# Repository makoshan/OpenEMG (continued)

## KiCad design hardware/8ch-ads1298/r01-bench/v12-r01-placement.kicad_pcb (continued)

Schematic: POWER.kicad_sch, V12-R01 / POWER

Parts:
C19: 10uF; C_0603_1608Metric
C20, C21: 22uF; C_0805_2012Metric
C22, C23, C24: 1uF; C_0402_1005Metric
C25, C31: 100nF; C_0402_1005Metric
D1: B5819WS; D_SOD-323
L1: 470nH; FTC201610S
Q1: AO3400A; SOT-23
R21, R25, R27, R29, R30, R31, R32: 100k; R_0402_1005Metric
R22, R28: 10k; R_0402_1005Metric
R23: 1k; R_0402_1005Metric
R24: 47k; R_0402_1005Metric
R26: 0R; R_0402_1005Metric
R41: 4.7k; R_0402_1005Metric
TP1: AVDD; TestPoint_Pad_D1.0mm
TP2: DVDD; TestPoint_Pad_D1.0mm
TP3: PG; TestPoint_Pad_D1.0mm
TP4: OE_N; TestPoint_Pad_D1.0mm
TP5: ADS_PWDN; TestPoint_Pad_D1.0mm
TP6: ADS_RESET; TestPoint_Pad_D1.0mm
TP7: ADS_CLKSEL; TestPoint_Pad_D1.0mm
TP8: VCAP1; TestPoint_Pad_D1.0mm
TP9: U7_EN; TestPoint_Pad_D1.0mm
TP10: GND; TestPoint_Pad_D1.0mm
U7: TPS63802DLAR; TI_DLA0010A
U9: TPS7A2018PDBVR; SOT-23-5
U12: TPS3808G33DBVR; SOT-23-6

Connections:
3V3: U12.5 (SENSE); also elsewhere on the board
ADS_CLKSEL: TP7.1; also elsewhere on the board
ADS_PWDN: TP5.1; also elsewhere on the board
ADS_RESET: TP6.1; also elsewhere on the board
ANA_EN: R24.1; also elsewhere on the board
AVDD: C20.1, C21.1, C22.1, D1.1 (K), R21.1, R29.1, TP1.1, U7.6 (VOUT), U9.1 (IN), U9.3 (EN); also elsewhere on the board
AVDD_SENSE: C25.1, R31.2, R32.1; also elsewhere on the board
AVS1: R29.2, R30.1
AVS2: R30.2, R31.1
DVDD: C23.1, D1.2 (A), R28.2, TP2.1, U9.5 (OUT); also elsewhere on the board
EN_RC: C24.1, R41.2
GND: C19.2, C20.2, C21.2, C22.2, C23.2, C24.2, C25.2, C31.2, Q1.2 (S), R23.2, R25.2, R27.2, R32.2, TP10.1, U7.3 (AGND), U7.8 (GND), U9.2 (GND), U12.2 (GND); also elsewhere on the board
ILK_D: Q1.3 (D), R26.1
OE_N: TP4.1; also elsewhere on the board
PG: R28.1, TP3.1, U7.5 (PG); also elsewhere on the board
U7_EN: R24.2, R25.1, R26.2, R41.1, TP9.1, U7.1 (EN), U12.1 (~RESET)
U7_FB: R21.2, R22.1, U7.4 (FB)
U7_FBL: R22.2, R23.1
U7_L1: L1.1, U7.9 (L1)
U7_L2: L1.2, U7.7 (L2)
VBAT: C19.1, C31.1, U7.2 (MODE), U7.10 (VIN), U12.3 (~MR), U12.6 (VDD); also elsewhere on the board
VBUS: Q1.1 (G), R27.1; also elsewhere on the board
VCAP1: TP8.1; also elsewhere on the board

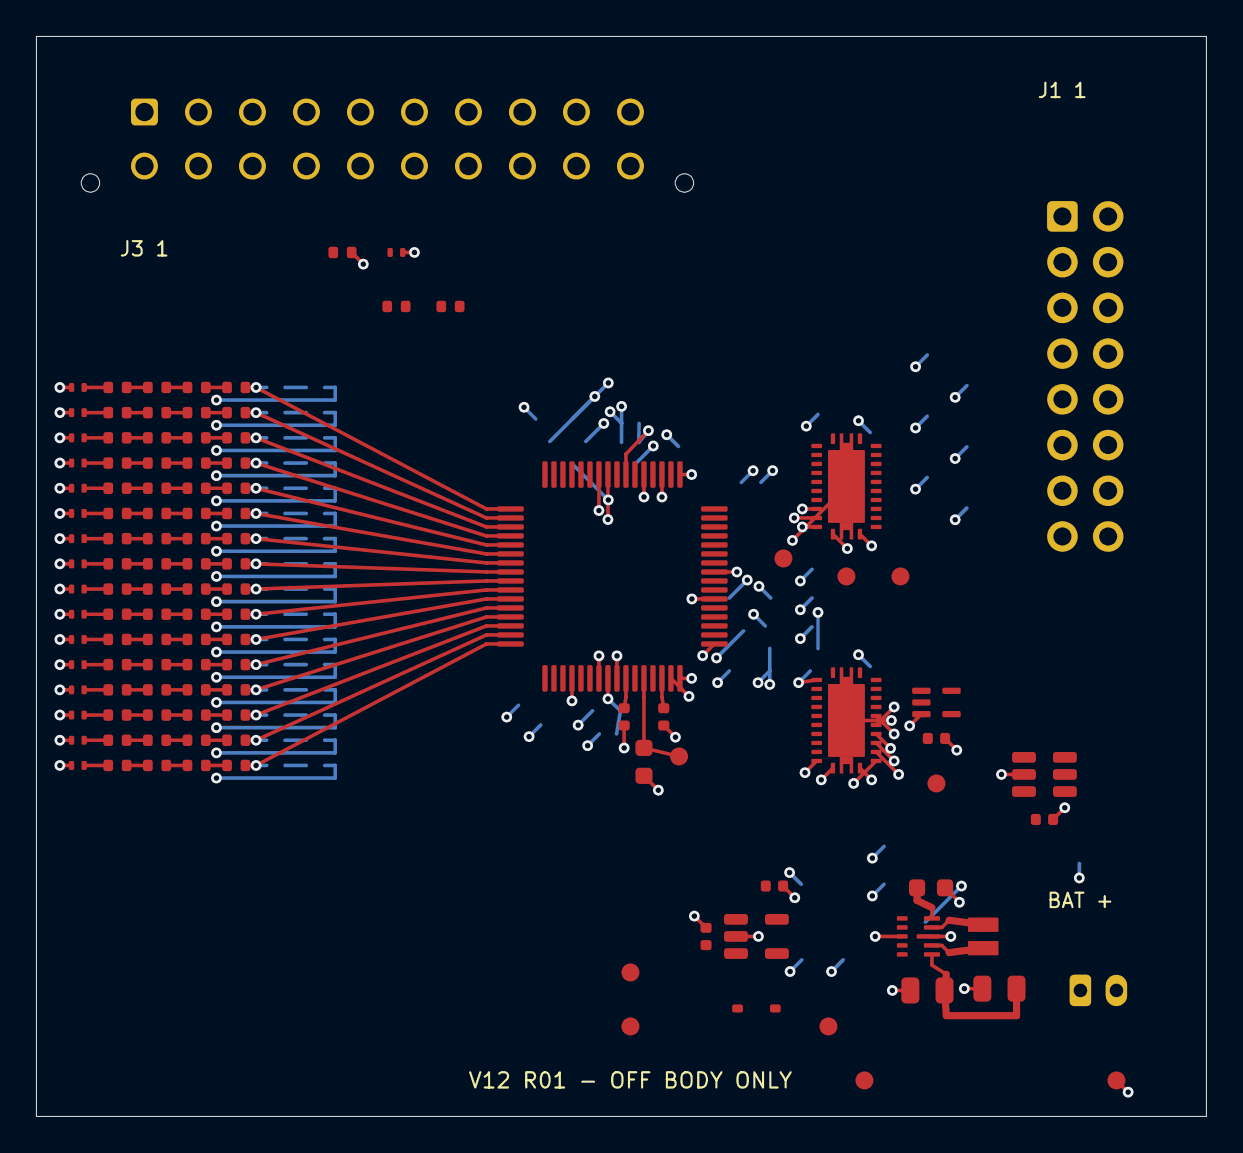
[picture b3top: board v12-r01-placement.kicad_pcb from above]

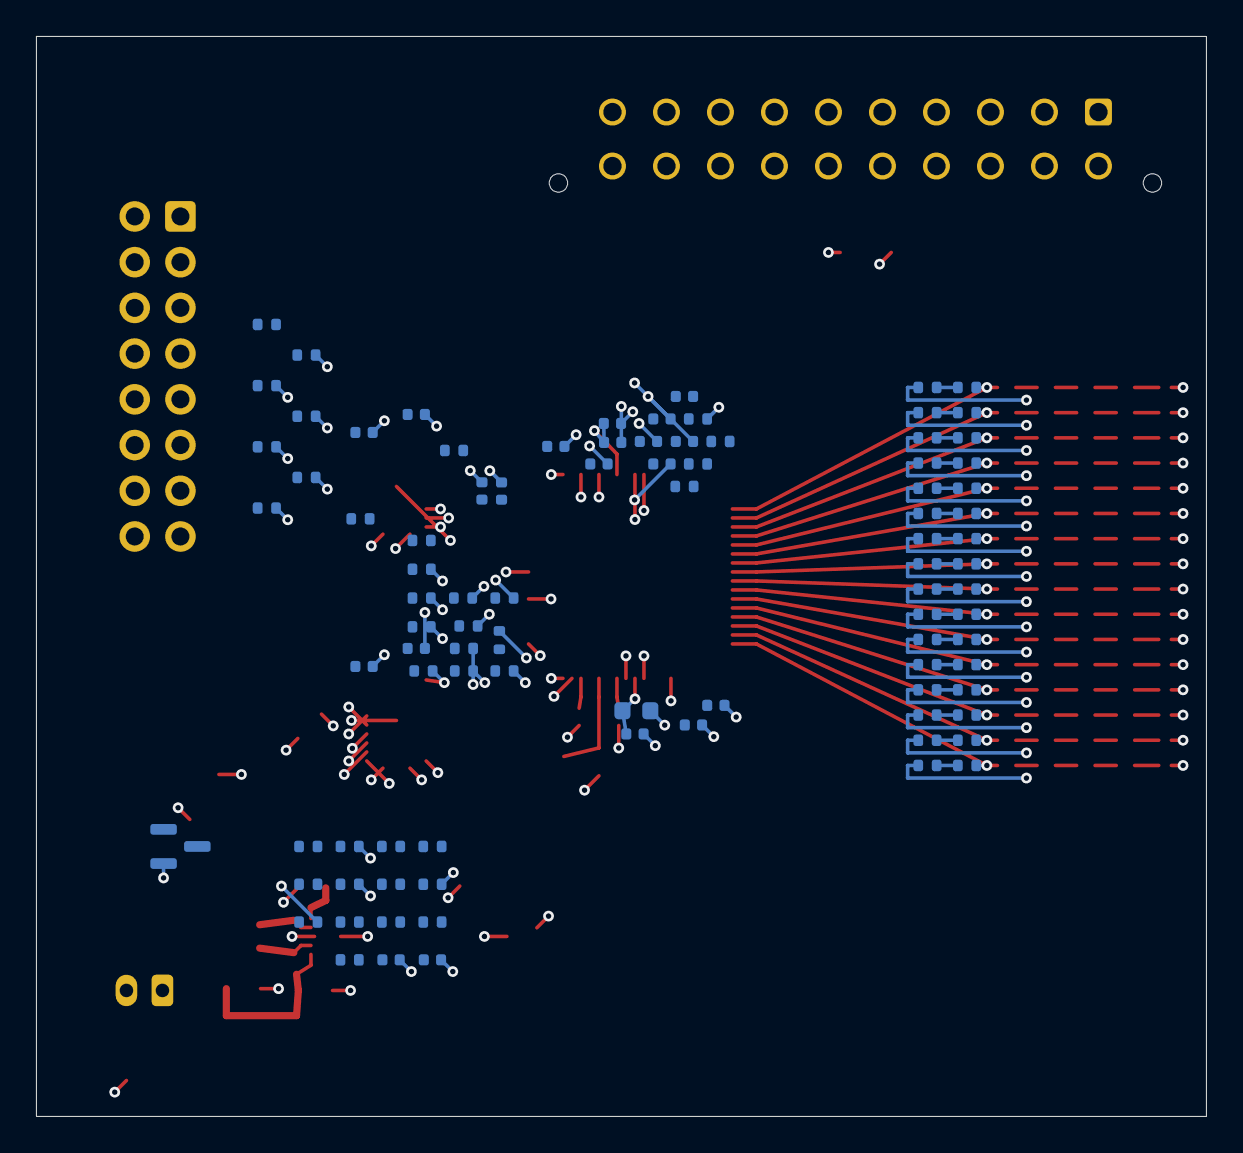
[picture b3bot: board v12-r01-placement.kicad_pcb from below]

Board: 4 copper layers, 65.0 x 60.0 mm, 208 parts (92 on the bottom side), 150 nets.

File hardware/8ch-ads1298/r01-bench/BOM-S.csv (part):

Reference,Value,LCSC,Footprint,Variant,Note
U1,ADS1298IPAGR,C527440,Package_QFP:TQFP-64_10x10mm_P0.5mm,S,RLDIN未用接AVDD；固件必须禁止RLD_MEAS及CHnSET的RLDIN路由。
C1,10uF,C19702,Capacitor_SMD:C_0603_1608Metric,S,
C2,1uF,C52923,Capacitor_SMD:C_0402_1005Metric,S,
C3,22uF,C59461,Capacitor_SMD:C_0603_1608Metric,S,有效电容/压电噪声待核
C4,1uF,C52923,Capacitor_SMD:C_0402_1005Metric,S,
C5,1uF,C52923,Capacitor_SMD:C_0402_1005Metric,S,
C6,100nF,C1525,Capacitor_SMD:C_0402_1005Metric,S,
C7,1uF,C52923,Capacitor_SMD:C_0402_1005Metric,S,
C8,1uF,C52923,Capacitor_SMD:C_0402_1005Metric,S,AVDD 脚 19/21/22
C9,100nF,C1525,Capacitor_SMD:C_0402_1005Metric,S,AVDD 脚 19/21/22
C10,1uF,C52923,Capacitor_SMD:C_0402_1005Metric,S,AVDD 脚 54 AVDD1
C11,100nF,C1525,Capacitor_SMD:C_0402_1005Metric,S,AVDD 脚 54 AVDD1
C12,1uF,C52923,Capacitor_SMD:C_0402_1005Metric,S,AVDD 脚 56/59
C13,100nF,C1525,Capacitor_SMD:C_0402_1005Metric,S,AVDD 脚 56/59
C14,100nF,C1525,Capacitor_SMD:C_0402_1005Metric,S,DVDD 脚 48
C15,100nF,C1525,Capacitor_SMD:C_0402_1005Metric,S,DVDD 脚 50
C16,1uF,C52923,Capacitor_SMD:C_0402_1005Metric,S,
R1,100k,C25741,Resistor_SMD:R_0402_1005Metric,S,
R2,100k,C25741,Resistor_SMD:R_0402_1005Metric,S,
C17,1uF,C52923,Capacitor_SMD:C_0402_1005Metric,S,
R3,200k,C25764,Resistor_SMD:R_0402_1005Metric,S,
R4,200k,C25764,Resistor_SMD:R_0402_1005Metric,S,
C18,10nF,C15195,Capacitor_SMD:C_0402_1005Metric,S,
R5,200k,C25764,Resistor_SMD:R_0402_1005Metric,S,
R6,200k,C25764,Resistor_SMD:R_0402_1005Metric,S,
R7,10M,C2933065,Resistor_SMD:R_0402_1005Metric,S,
ESD17,ESD501DPYR,C42409135,Package_SON:Texas_DPY0002A_0.6x1mm_P0.65mm,S,
R8,33R,C25105,Resistor_SMD:R_0402_1005Metric,S,
R9,33R,C25105,Resistor_SMD:R_0402_1005Metric,S,
R10,33R,C25105,Resistor_SMD:R_0402_1005Metric,S,
R11,10k,C25744,Resistor_SMD:R_0402_1005Metric,S,
R12,10k,C25744,Resistor_SMD:R_0402_1005Metric,S,
R13,10k,C25744,Resistor_SMD:R_0402_1005Metric,S,
R14,10k,C25744,Resistor_SMD:R_0402_1005Metric,S,
R15,10k,C25744,Resistor_SMD:R_0402_1005Metric,S,
R16,10k,C25744,Resistor_SMD:R_0402_1005Metric,S,
R17,10k,C25744,Resistor_SMD:R_0402_1005Metric,S,
R18,10k,C25744,Resistor_SMD:R_0402_1005Metric,S,
R19,10k,C25744,Resistor_SMD:R_0402_1005Metric,S,
R20,10k,C25744,Resistor_SMD:R_0402_1005Metric,S,
ESD1,ESD501DPYR,C42409135,Package_SON:Texas_DPY0002A_0.6x1mm_P0.65mm,S,
R101,1M,C26083,Resistor_SMD:R_0402_1005Metric,S,
R102,1M,C26083,Resistor_SMD:R_0402_1005Metric,S,
R103,1M,C26083,Resistor_SMD:R_0402_1005Metric,S,
R104,1M,C26083,Resistor_SMD:R_0402_1005Metric,S,
R105,10M,C2933065,Resistor_SMD:R_0402_1005Metric,S,
R106,10M,C2933065,Resistor_SMD:R_0402_1005Metric,S,
ESD2,ESD501DPYR,C42409135,Package_SON:Texas_DPY0002A_0.6x1mm_P0.65mm,S,
R107,1M,C26083,Resistor_SMD:R_0402_1005Metric,S,
R108,1M,C26083,Resistor_SMD:R_0402_1005Metric,S,
R109,1M,C26083,Resistor_SMD:R_0402_1005Metric,S,
R110,1M,C26083,Resistor_SMD:R_0402_1005Metric,S,
R111,10M,C2933065,Resistor_SMD:R_0402_1005Metric,S,
R112,10M,C2933065,Resistor_SMD:R_0402_1005Metric,S,
ESD3,ESD501DPYR,C42409135,Package_SON:Texas_DPY0002A_0.6x1mm_P0.65mm,S,
R113,1M,C26083,Resistor_SMD:R_0402_1005Metric,S,
R114,1M,C26083,Resistor_SMD:R_0402_1005Metric,S,
R115,1M,C26083,Resistor_SMD:R_0402_1005Metric,S,
R116,1M,C26083,Resistor_SMD:R_0402_1005Metric,S,
R117,10M,C2933065,Resistor_SMD:R_0402_1005Metric,S,
R118,10M,C2933065,Resistor_SMD:R_0402_1005Metric,S,
ESD4,ESD501DPYR,C42409135,Package_SON:Texas_DPY0002A_0.6x1mm_P0.65mm,S,
R119,1M,C26083,Resistor_SMD:R_0402_1005Metric,S,
R120,1M,C26083,Resistor_SMD:R_0402_1005Metric,S,
R121,1M,C26083,Resistor_SMD:R_0402_1005Metric,S,
R122,1M,C26083,Resistor_SMD:R_0402_1005Metric,S,
R123,10M,C2933065,Resistor_SMD:R_0402_1005Metric,S,
R124,10M,C2933065,Resistor_SMD:R_0402_1005Metric,S,
ESD5,ESD501DPYR,C42409135,Package_SON:Texas_DPY0002A_0.6x1mm_P0.65mm,S,
R125,1M,C26083,Resistor_SMD:R_0402_1005Metric,S,
R126,1M,C26083,Resistor_SMD:R_0402_1005Metric,S,
R127,1M,C26083,Resistor_SMD:R_0402_1005Metric,S,
R128,1M,C26083,Resistor_SMD:R_0402_1005Metric,S,
R129,10M,C2933065,Resistor_SMD:R_0402_1005Metric,S,
R130,10M,C2933065,Resistor_SMD:R_0402_1005Metric,S,
ESD6,ESD501DPYR,C42409135,Package_SON:Texas_DPY0002A_0.6x1mm_P0.65mm,S,
R131,1M,C26083,Resistor_SMD:R_0402_1005Metric,S,
R132,1M,C26083,Resistor_SMD:R_0402_1005Metric,S,
R133,1M,C26083,Resistor_SMD:R_0402_1005Metric,S,
R134,1M,C26083,Resistor_SMD:R_0402_1005Metric,S,
R135,10M,C2933065,Resistor_SMD:R_0402_1005Metric,S,
R136,10M,C2933065,Resistor_SMD:R_0402_1005Metric,S,
ESD7,ESD501DPYR,C42409135,Package_SON:Texas_DPY0002A_0.6x1mm_P0.65mm,S,
R137,1M,C26083,Resistor_SMD:R_0402_1005Metric,S,
R138,1M,C26083,Resistor_SMD:R_0402_1005Metric,S,
R139,1M,C26083,Resistor_SMD:R_0402_1005Metric,S,
R140,1M,C26083,Resistor_SMD:R_0402_1005Metric,S,
R141,10M,C2933065,Resistor_SMD:R_0402_1005Metric,S,
R142,10M,C2933065,Resistor_SMD:R_0402_1005Metric,S,
ESD8,ESD501DPYR,C42409135,Package_SON:Texas_DPY0002A_0.6x1mm_P0.65mm,S,
R143,1M,C26083,Resistor_SMD:R_0402_1005Metric,S,
R144,1M,C26083,Resistor_SMD:R_0402_1005Metric,S,
R145,1M,C26083,Resistor_SMD:R_0402_1005Metric,S,
R146,1M,C26083,Resistor_SMD:R_0402_1005Metric,S,
R147,10M,C2933065,Resistor_SMD:R_0402_1005Metric,S,
R148,10M,C2933065,Resistor_SMD:R_0402_1005Metric,S,
ESD9,ESD501DPYR,C42409135,Package_SON:Texas_DPY0002A_0.6x1mm_P0.65mm,S,
R149,1M,C26083,Resistor_SMD:R_0402_1005Metric,S,
R150,1M,C26083,Resistor_SMD:R_0402_1005Metric,S,
R151,1M,C26083,Resistor_SMD:R_0402_1005Metric,S,
R152,1M,C26083,Resistor_SMD:R_0402_1005Metric,S,
R153,10M,C2933065,Resistor_SMD:R_0402_1005Metric,S,
R154,10M,C2933065,Resistor_SMD:R_0402_1005Metric,S,
ESD10,ESD501DPYR,C42409135,Package_SON:Texas_DPY0002A_0.6x1mm_P0.65mm,S,
R155,1M,C26083,Resistor_SMD:R_0402_1005Metric,S,
R156,1M,C26083,Resistor_SMD:R_0402_1005Metric,S,
R157,1M,C26083,Resistor_SMD:R_0402_1005Metric,S,
R158,1M,C26083,Resistor_SMD:R_0402_1005Metric,S,
R159,10M,C2933065,Resistor_SMD:R_0402_1005Metric,S,
R160,10M,C2933065,Resistor_SMD:R_0402_1005Metric,S,
ESD11,ESD501DPYR,C42409135,Package_SON:Texas_DPY0002A_0.6x1mm_P0.65mm,S,
R161,1M,C26083,Resistor_SMD:R_0402_1005Metric,S,
R162,1M,C26083,Resistor_SMD:R_0402_1005Metric,S,
R163,1M,C26083,Resistor_SMD:R_0402_1005Metric,S,
R164,1M,C26083,Resistor_SMD:R_0402_1005Metric,S,
R165,10M,C2933065,Resistor_SMD:R_0402_1005Metric,S,
R166,10M,C2933065,Resistor_SMD:R_0402_1005Metric,S,
ESD12,ESD501DPYR,C42409135,Package_SON:Texas_DPY0002A_0.6x1mm_P0.65mm,S,
R167,1M,C26083,Resistor_SMD:R_0402_1005Metric,S,
R168,1M,C26083,Resistor_SMD:R_0402_1005Metric,S,
R169,1M,C26083,Resistor_SMD:R_0402_1005Metric,S,
R170,1M,C26083,Resistor_SMD:R_0402_1005Metric,S,
R171,10M,C2933065,Resistor_SMD:R_0402_1005Metric,S,
R172,10M,C2933065,Resistor_SMD:R_0402_1005Metric,S,
ESD13,ESD501DPYR,C42409135,Package_SON:Texas_DPY0002A_0.6x1mm_P0.65mm,S,
R173,1M,C26083,Resistor_SMD:R_0402_1005Metric,S,
R174,1M,C26083,Resistor_SMD:R_0402_1005Metric,S,
R175,1M,C26083,Resistor_SMD:R_0402_1005Metric,S,
R176,1M,C26083,Resistor_SMD:R_0402_1005Metric,S,
R177,10M,C2933065,Resistor_SMD:R_0402_1005Metric,S,
R178,10M,C2933065,Resistor_SMD:R_0402_1005Metric,S,
ESD14,ESD501DPYR,C42409135,Package_SON:Texas_DPY0002A_0.6x1mm_P0.65mm,S,
R179,1M,C26083,Resistor_SMD:R_0402_1005Metric,S,
R180,1M,C26083,Resistor_SMD:R_0402_1005Metric,S,
R181,1M,C26083,Resistor_SMD:R_0402_1005Metric,S,
R182,1M,C26083,Resistor_SMD:R_0402_1005Metric,S,
R183,10M,C2933065,Resistor_SMD:R_0402_1005Metric,S,
R184,10M,C2933065,Resistor_SMD:R_0402_1005Metric,S,
ESD15,ESD501DPYR,C42409135,Package_SON:Texas_DPY0002A_0.6x1mm_P0.65mm,S,
R185,1M,C26083,Resistor_SMD:R_0402_1005Metric,S,
R186,1M,C26083,Resistor_SMD:R_0402_1005Metric,S,
R187,1M,C26083,Resistor_SMD:R_0402_1005Metric,S,
R188,1M,C26083,Resistor_SMD:R_0402_1005Metric,S,
R189,10M,C2933065,Resistor_SMD:R_0402_1005Metric,S,
R190,10M,C2933065,Resistor_SMD:R_0402_1005Metric,S,
ESD16,ESD501DPYR,C42409135,Package_SON:Texas_DPY0002A_0.6x1mm_P0.65mm,S,
R191,1M,C26083,Resistor_SMD:R_0402_1005Metric,S,
R192,1M,C26083,Resistor_SMD:R_0402_1005Metric,S,
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
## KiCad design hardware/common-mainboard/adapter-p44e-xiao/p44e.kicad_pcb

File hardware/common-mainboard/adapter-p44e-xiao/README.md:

# P44e：ADS1292 载板专用 XIAO 转接板

2026-11-06，Mako 定「改薄重出」。**已实现未验收**，未下单、未打样。从 P44d（P44d，文件没动）改出，`make_p44e.py` 可重建，改完用 `kicad-cli pcb drc --refill-zones --save-board` 重铺。

**只能配 ADS1292 载板，不能插 V4**：J1 19 脚是 5 V，V4 这只脚是 CS#4。背面丝印写了 `P44e ADS1292 ONLY`。

| 项 | P44d | P44e |
|---|---|---|
| 板厚 | 1.6 | **0.8** |
| J1 19 脚 | 空 | **XIAO 5V** |
| J1 14 脚 | RESET_N | 空 |
| J1 17 脚 | CS_B | 空 |
| 外形、BAT 槽、J1、阻容、天线禁区 | | 不变 |

脚网和 P44d 只差这 4 处：U1.14、J1.19 新接 5V，J1.14、J1.17 断开。D0、D2 的上拉 R2、R5 留着。14、17 脚载板不用，断开是为了让 19 脚有路。

- `pin-table.csv`：J1 脚表，载板 `design.py` 读它。
- `fab-20261106/`：Gerber、钻孔、BOM、坐标，`make_fab.py` 生成。钢网只开背面。
- `jlc-eda/`：嘉立创专业版单文件工程 `P44e-XIAO转接板-0.8mm-PCB+3D.epro2`（SHA-256 前 8 位 `3fc30545`，8/8 3D，DRC 0），供客户端查看与 3D 核对；光板下单仍传 `fab-20261106/` Gerber。
- DRC：重铺和不重铺都是 0 错 0 警 0 未连。

下单要点：FR-4，2 层，**0.8 mm**，5 片。生产稿要核 3.1×3.7 BAT 槽保留且铣通。J1 脚距 0.5，表面处理按 P44d 的取舍另定。

装法同 P44d（`README.md` C 节），电池线先焊 XIAO 背面穿槽，再焊邮票孔。

P44d 单（华秋 3849421）这块板不再用，取不取消由 Mako 定。

没验证：0.8 mm 板回流翘曲、邮票孔可焊性、XIAO 5V 焊盘在只用电池时的电平（载板 R25 10 kΩ 下拉，按低看待）、实物。

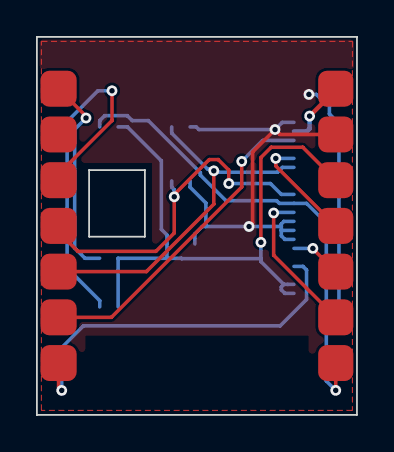
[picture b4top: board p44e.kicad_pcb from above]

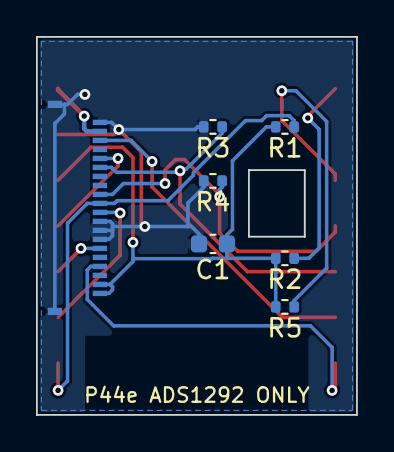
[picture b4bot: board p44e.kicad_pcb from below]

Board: 2 copper layers, 17.8 x 21.0 mm, 8 parts (7 on the bottom side), 13 nets.

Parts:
C1: 10uF; C_0603_1608Metric
J1: FH34SRJ-20S-0.5SH(50) (LCSC C2802370); Hirose_FH34SRJ-20S-0.5SH
R1, R2, R3, R4, R5: 10k; R_0402_1005Metric
U1: XIAO nRF52840 (Sense); XIAO-nRF52840-SMD

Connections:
3V3: C1.1, J1.1, J1.2, R1.2, R2.2, R5.2, U1.12
5V: J1.19, U1.14
CS_A: J1.11, R1.1, U1.8
CS_B: R2.1, U1.1
DRDY_A: J1.4, U1.7
DRDY_B: J1.18, U1.6
GND: C1.2, J1.7, J1.8, J1.9, J1.20, J1.21, J1.22, R3.2, R4.2, U1.13
MISO: J1.6, U1.10
MOSI: J1.16, U1.11
PWDN_N: J1.15, R3.1, U1.5
RESET_N: R5.1, U1.3
SCLK: J1.10, U1.9
START: J1.12, R4.1, U1.4

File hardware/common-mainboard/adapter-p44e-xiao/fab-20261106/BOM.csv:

Comment,Designator,Footprint,LCSC Part #,焊法
10kΩ 0402 1%,"R1,R2,R3,R4,R5",R_0402_1005Metric,C25744,加热台回流
10uF 10V 0603 X5R,C1,C_0603_1608Metric,C19702,加热台回流
FH34SRJ-20S-0.5SH(50),J1,Hirose_FH34SRJ-20S-0.5SH,C2802370,加热台回流；翻盖别烫
Seeed XIAO nRF52840 Sense,U1,XIAO-nRF52840-SMD,C17401557,最后烙铁手焊邮票孔；普通版 C17209540 也可

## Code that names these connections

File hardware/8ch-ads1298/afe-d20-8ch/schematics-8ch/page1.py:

"""C08A 第 1 页：两颗 ADS1298 采集核心。12 颗 ADS 去耦（V4_C31–C36 正面 U1、V4_C117–C122 背面 U2）从原第 3 页移来贴芯片画。
两颗 ADS 画法相同，用 ads() 按偏移复用；64 脚按 R10：输入/数字口用贴脚标签，电源、参考、VCAP、RLD/WCT 回路用实线。"""
import json
from sch import *

DECAP = ['V4_C31', 'V4_C32', 'V4_C33', 'V4_C34', 'V4_C35', 'V4_C36']
PAGE_REFS = [r for r in json.loads((SRC / 'page-map.json').read_text())[0]['refs'] + DECAP if r not in GONE]

# ADS1298 PAG 脚位：左=模拟输入与测试脚，右=数字口与地，上=电源与 RLD/WCT，下=负电源/参考/VCAP/NC
INPUTS = [(str(16 - i), ('IN%d%s' % (i // 2 + 1, 'P' if i % 2 == 0 else 'N'))) for i in range(16)]
SIGNALS = [('34', 'DIN'), ('40', 'SCLK'), ('39', 'CS'), ('43', 'DOUT'), ('47', 'DRDY'), ('38', 'START'), ('36', 'RESET'),
           ('35', 'PWDN'), ('37', 'CLK'), ('45', 'GPIO3'), ('52', 'CLKSEL')]
GNDS = [('41', 'DAISY_IN'), ('42', 'GPIO1'), ('44', 'GPIO2'), ('46', 'GPIO4'), ('31', 'RESV1'), ('33', 'DGND'), ('49', 'DGND'),
        ('51', 'DGND'), ('60', 'RLDREF'), ('62', 'RLDIN')]
AVDD, AVSS, DVDD = ['19', '21', '22', '54', '56', '59'], ['20', '23', '25', '32', '53', '57', '58'], ['48', '50']

def capq(ref, x, y, o):
    """竖向电容，标注三行（位号/料值/8路不贴），给底排 66 间距用；连接与 sch.cap 相同。"""
    a, b = (x, y - 40), (x, y + 40)
    if o == 'vr': a, b = b, a
    pin(ref, '1', *a); pin(ref, '2', *b)
    line([(x, y - 40), (x, y - 4)]); line([(x, y + 4), (x, y + 40)])
    line([(x - 12, y - 4), (x + 12, y - 4)], w=2); line([(x - 12, y + 4), (x + 12, y + 4)], w=2)
    v, c = val(ref).split(' 8路不贴')[0], tcol(ref)
    text(ref, x + 12, y - 3, color=c); text(v, x + 12, y + 11, color=c)
    if ref in DNP8: text('8路不贴', x + 12, y + 25, color=c)

def tp(ref, x, y):
    """测试点：圆在右，脚朝左。"""
    pin(ref, '1', x - 20, y); line([(x - 20, y), (x - 6, y)])
    svg.append(f'<circle cx="{x}" cy="{y}" r="6" fill="none" stroke="{SYM}" stroke-width="1.4"/>')
    text(ref, x + 10, y + 4)

def ads(dx, u, c, title, note):
    """c：本颗外围件位号表。dx：整框横向偏移。"""
    x0, y0, w, h = 200 + dx, 290, 480, 430
    block(30 + dx, 60, 830 + dx, 910, title, note)
    pins = [(n, nm, 'L', 20 + 20 * i) for i, (n, nm) in enumerate(INPUTS)] + [('17', 'TESTP', 'L', 350), ('18', 'TESTN', 'L', 370)]
    pins += [(n, nm, 'R', 60 + 20 * i) for i, (n, nm) in enumerate(SIGNALS)] + [(n, nm, 'R', 285 + 13 * i) for i, (n, nm) in enumerate(GNDS)]
    pins += [(n, '', 'T', 50 + 20 * i) for i, n in enumerate(DVDD)] + [(n, '', 'T', 110 + 20 * i) for i, n in enumerate(AVDD)]
    pins += [('61', 'RLDINV', 'T', 250), ('63', 'RLDOUT', 'T', 330), ('64', 'WCT', 'T', 460)]
    pins += [(n, '', 'B', 12 + 12 * i) for i, n in enumerate(AVSS)] + [('27', '', 'B', 100), ('29', '', 'B', 115)]
    pins += [('24', 'VREFP', 'B', 130), ('26', 'VCAP4', 'B', 262), ('28', 'VCAP1', 'B', 328), ('30', 'VCAP2', 'B', 394), ('55', 'VCAP3', 'B', 460)]
    ic(u, x0, y0, w, h, pins)
    text('DVDD', x0 + 60, y0 + 30, size=10, color=SYM, anchor='middle')
    text('AVDD ×6', x0 + 160, y0 + 30, size=10, color=SYM, anchor='middle')
    text('AVSS ×7（含 VREFN）', x0 + 60, y0 + h - 22, size=10, color=SYM, anchor='middle')
    # 输入、测试脚、数字口：贴脚标签
    for n, _ in INPUTS + [('17', ''), ('18', '')]: lab(EXPECT[(u, n)], *Pn(u, n), 'left')
    for n, _ in SIGNALS[:-1]: lab(EXPECT[(u, n)], *Pn(u, n), 'right')
    # 数字地一排用竖线并到一个地符号
    # D16 分地：RLDREF、RLDIN 接 AGND，其余接 GND（RESV1、DAISY_IN、未用 GPIO 都要逻辑低）
    px, py = Pn(u, '51'); wire(Pn(u, GNDS[0][0]), Pn(u, '51'), (px + 30, py)); dgnd(px + 30, py, 'right')
    wire(Pn(u, '60'), Pn(u, '62')); gnd(*Pn(u, '62'))
    nc(*Pn(u, '27')); nc(*Pn(u, '29'))
    # DVDD → 3V3 去耦（1µF + 100nF）
    wire(Pn(u, DVDD[0]), Pn(u, DVDD[1])); wire(Pn(u, DVDD[0]), (x0 + 50, 150), (60 + dx, 150))
    cap(c['d3a'], 60 + dx, 190, 'vr'); cap(c['d3b'], 122 + dx, 190, 'vr'); dgnd(*Pn(c['d3a'], '1'), 'right'); dgnd(*Pn(c['d3b'], '1'), 'right')
    pwr('3V3', 180 + dx, 150)
    # AVDD → +2.5V 去耦
    wire(Pn(u, AVDD[0]), Pn(u, AVDD[-1])); wire(Pn(u, AVDD[0]), (x0 + 110, 150), (386 + dx, 150))
    cap(c['d25a'], 326 + dx, 190, 'vr'); cap(c['d25b'], 386 + dx, 190, 'vr'); gnd(*Pn(c['d25a'], '1')); gnd(*Pn(c['d25b'], '1'))
    pwr('V4_+2.5V', 356 + dx, 150)
    # RLD：RLDOUT 经 392k∥10nF 回 RLDINV，再经 392k 出偏置驱动
    res(c['rf'], 490 + dx, 220, 'h'); cap(c['cf'], 490 + dx, 160, 'h')
    wire(Pn(u, '61'), Pn(c['rf'], '1'), Pn(c['cf'], '1')); wire(Pn(u, '63'), Pn(c['rf'], '2'), Pn(c['cf'], '2'))
    res(c['rb'], 600 + dx, 160, 'h'); wire(Pn(c['cf'], '2'), Pn(c['rb'], '1')); lab(EXPECT[(c['rb'], '2')], *Pn(c['rb'], '2'), 'right')
    # WCT：100pF 到地，10k 引到电极座
    wire(Pn(u, '64'), (x0 + 460, 232), (690 + dx, 232))   # 上移 8，地符号不压 34 脚脚号
    cap(c['cw'], 690 + dx, 272, 'v'); gnd(*Pn(c['cw'], '2'))
    res(c['rw'], 730 + dx, 232, 'h'); lab(EXPECT[(c['rw'], '2')], *Pn(c['rw'], '2'), 'right')
    # 负电源母线：AVSS 直下，VREFP/VCAP 电容挂在母线上
    bus = 870
    for n in AVSS: wire(Pn(u, n), (Pn(u, n)[0], bus))
    capq(c['vr1'], x0 + 130, 830, 'vr'); capq(c['vr2'], x0 + 196, 830, 'v')
    wire(Pn(u, '24'), Pn(c['vr1'], '2')); wire((x0 + 130, 765), (x0 + 196, 765), Pn(c['vr2'], '1'))
    for n, k in (('26', 'vc4'), ('28', 'vc1'), ('30', 'vc2')):
        capq(c[k], Pn(u, n)[0], 830, 'vr'); wire(Pn(u, n), Pn(c[k], '2'))
    capq(c['vc3a'], x0 + 460, 830, 'vr'); capq(c['vc3b'], x0 + 526, 830, 'v')
    wire(Pn(u, '55'), Pn(c['vc3a'], '2')); wire((x0 + 460, 765), (x0 + 526, 765), Pn(c['vc3b'], '1'))
    # ±2.5V 跨接去耦挂在母线左端
    SIDE[c['dpm_a']] = 1  # 左边那颗标注放左侧，免得压到右侧母线
    cap(c['dpm_a'], 100 + dx, 830, 'vr'); cap(c['dpm_b'], 150 + dx, 830, 'vr')
    wire(Pn(c['dpm_a'], '2'), Pn(c['dpm_b'], '2')); pwr('V4_+2.5V', 125 + dx, Pn(c['dpm_a'], '2')[1])
    wire((64 + dx, bus), (x0 + 526, bus)); pwr('V4_-2.5V', 64 + dx, bus, up=False)
    text('VREFP / VCAP 电容都接 -2.5V', x0 + 200, 897, color='#555')

DX1 = 410
U1 = dict(d3a='V4_C31', d3b='V4_C32', d25a='V4_C33', d25b='V4_C34', dpm_a='V4_C35', dpm_b='V4_C36', rf='V4_R24', cf='V4_C47', rb='V4_R34',
          cw='V4_C123', rw='V4_R35', vr1='V4_C45', vr2='V4_C46', vc4='V4_C44', vc1='V4_C54', vc2='V4_C43', vc3a='V4_C48', vc3b='V4_C49')
ads(DX1, 'V4_U1', U1, 'A  ADS1298 采集核心（U1，正面单面贴）：电极 CH1–8 → SPI', '±2.5V 双电源；RLD 偏置经 392k∥10nF 反馈、392k 出 V4_BIAS_DRV1；WCT 100pF 滤波后引到电极座')
# CLKSEL 下拉
lab('ADS_CLKSEL', 740 + DX1, Pn('V4_U1', '52')[1], 'right'); wire(Pn('V4_U1', '52'), (740 + DX1, Pn('V4_U1', '52')[1]))
res('V4_R17', 720 + DX1, Pn('V4_U1', '52')[1] + 40, 'vr'); dgnd(*Pn('V4_R17', '1'), 'right')

# ---------------- B 时钟与测试点 ----------------
block(30, 925, 1650, 1080, 'B  AFE 时钟与测试点：2.048MHz 有源晶振 → AFE_CLK_IN', '晶振供 U1，AFE_CLK_IN 也引到 J_AFE（主控未用）；TP901/TP902 引出 TESTP/TESTN 测点；V4_R18 0R 是数字地 GND 和模拟地 AGND 的唯一连接；未标名地符号都是 AGND。')
ic('V4_X1', 260, 1000, 110, 50, [('4', 'VDD', 'L', 15), ('1', 'EN', 'L', 40), ('3', 'OUT', 'R', 15), ('2', 'GND', 'B', 55)])
wire(Pn('V4_X1', '4'), (200, 1015), (200, 1040), Pn('V4_X1', '1')); pwr('3V3', 200, 1015)
cap('V4_C37', 140, 1040, 'h'); wire(Pn('V4_C37', '2'), (200, 1040)); dgnd(*Pn('V4_C37', '1')); dgnd(*Pn('V4_X1', '2'))
lab('AFE_CLK_IN', *Pn('V4_X1', '3'), 'right')
for i, r in enumerate(['TP902', 'TP901']):
    x, y = 760, 1005 + 40 * i
    tp(r, x, y); lab(EXPECT[(r, '1')], *Pn(r, '1'), 'left')
res('V4_R18', 1300, 1010, 'h'); dgnd(*Pn('V4_R18', '1')); gnd(*Pn('V4_R18', '2'), label='AGND', side='right')

finish(1, '单 ADS1298 采集', PAGE_REFS, 'C08B 单面 8 通道采集板：8 路电极 → 正面 ADS1298（U1）→ SPI 经 J_AFE',
       '正面单面贴 8 路（背面无器件，整面阻焊铜皮贴锂电池）；输入来自第 2 页保护，±2.5V 来自第 3 页，SPI/DRDY/CS 经 J_AFE 去主控板。')

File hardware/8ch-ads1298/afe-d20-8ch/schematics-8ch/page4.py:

"""C08B 采集板 第 4 页：J_AFE 板对板接口。FH34SRJ-20S 把采集板的 SPI/控制/时钟（接 P1 两颗 ADS）、
3V3（来自主控板）、GND 引到主控板。座子是 derive 加的、不在 C08A 真源，本页把它的脚→网补进 EXPECT 再逐脚比对。"""
import json
from sch import *

JAFE = {'1': 'GND', '2': '', '3': '', '4': '', '5': 'DIN_B', '6': 'ADS_PWDN',
        '7': 'ADS_RESET', '8': 'AFE_CLK_IN', '9': 'ADS_START', '10': 'ADS_CS_A', '11': 'SCLK_B',
        '12': 'GND', '13': '', '14': 'GND', '15': 'DOUT_B', '16': 'AFE_GPIO3', '17': 'ADS_DRDY_A',
        '18': 'ADS_CLKSEL', '19': '3V3', '20': '3V3', '21': 'GND', '22': 'GND'}
EXPECT.update({('J_AFE', p): n for p, n in JAFE.items()})
VAL['J_AFE'] = 'FH34SRJ-20S-0.5SH'
PULLS = [('R801', 'ADS_CS_A', 1), ('R803', 'ADS_RESET', 0), ('R804', 'ADS_PWDN', 0),
         ('R805', 'ADS_START', 0), ('R806', 'SCLK_B', 0), ('R807', 'DIN_B', 0), ('R808', 'AFE_GPIO3', 0)]
PAGE_REFS = ['J_AFE'] + [r for r, _, _ in PULLS]

block(30, 60, 1100, 1080, 'A  J_AFE 板对板接口：FH34SRJ-20S（0.5 mm 20 芯）→ 主控板',
      'SPI/控制/时钟接 P1 正面 U1；19/20 脚 3V3 由主控板供入（去 P3）；1/12/14/21/22 脚 GND；2/3/4/13 脚空（无背面从片 U2）。与主控板 J_AFE 对插兼容。')

x0, y0, w, h = 760, 200, 160, 640
left = [str(i) for i in range(1, 12)]        # 1–11 左
right = [str(i) for i in range(12, 23)]      # 12–22 右
pins = [(n, JAFE[n] or 'NC', 'L', 20 + 40 * i) for i, n in enumerate(left)]
pins += [(n, JAFE[n] or 'NC', 'R', 20 + 40 * i) for i, n in enumerate(right)]
ic('J_AFE', x0, y0, w, h, pins, name='FH34SRJ-20S')

for num, net in JAFE.items():
    x, y = Pn('J_AFE', num)
    d = 'left' if num in left else 'right'
    if net == '':
        nc(x, y)
    elif net == 'GND':
        dgnd(x, y, d)   # 标名放外侧，不压座子方框
    elif net == '3V3':
        lab('3V3', x, y, d)   # 脚距小，电源旗会压到上一行，用和信号一样的端口
    else:
        lab(net, x, y, d)

# B 框：主控板没插或上电前，片选默认拉高（不选中 ADS），其余控制/时钟/数据线默认拉低
block(1130, 60, 1650, 1080, 'B  J_AFE 信号上下拉：R801、R803–R808',
      '主控板未接时：CS_A 拉高（不选中），RESET/PWDN/START/SCLK/DIN/GPIO3 拉低；10 kΩ。')
for i, (r, net, up) in enumerate(PULLS):
    y = 170 + 105 * i
    lab(net, 1250, y, 'left'); wire((1250, y), (1360, y))
    res(r, 1400, y, 'h'); wire(Pn(r, '2'), (1480, y))
    pwr('3V3', 1480, y) if up else dgnd(1480, y)

finish(4, 'J_AFE 接口', PAGE_REFS, 'C08B 单面 8 通道采集板 J_AFE：20 芯板对板座，SPI/控制/时钟接 U1、3V3 自主控板',
       '信号脚旗标接 P1 的正面 ADS1298（U1）；3/4 脚（原从片 DRDY_B/CS_B）打叉悬空；与主控板 R4U6 / R4U6N 对插逐脚兼容。')

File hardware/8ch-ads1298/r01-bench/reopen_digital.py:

"""只撤回冲突的数字全局路由，保留已验证的局部引出；清除冗余输入地扇出。"""
from pathlib import Path
import wx
app=wx.App(False)
import pcbnew as k
P=Path(__file__).resolve().parent;b=k.LoadBoard(str(P/'v12-r01.kicad_pcb'));fp=next(f for f in b.GetFootprints() if f.GetReference()=='U3')
groundpads=[p.GetPosition() for p in fp.Pads() if p.GetNumber() in ('14','15','16','17','18','19')]
tracks=list(b.GetTracks());ends=[];drop=[]
for t in tracks:
 if t.GetNetname() in ('ADS_DRDY','DOUT_B','ADS_GPIO1','ADS_GPIO2','ADS_GPIO3','ADS_GPIO4') or (t.GetNetname()=='XIAO_DRDY' and not t.IsLocked()):drop.append(t);continue
 if t.GetNetname()=='GND' and type(t).__name__=='PCB_TRACK':
  if any(t.GetStart()==p for p in groundpads):ends.append(t.GetEnd());drop.append(t)
  elif any(t.GetEnd()==p for p in groundpads):ends.append(t.GetStart());drop.append(t)
for t in tracks:
 if type(t).__name__=='PCB_VIA' and t.GetNetname()=='GND' and any(t.GetPosition()==p for p in ends):drop.append(t)
for t in drop:b.Remove(t)
k.SaveBoard(str(P/'v12-r01.kicad_pcb'),b)

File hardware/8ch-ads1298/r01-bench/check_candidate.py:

"""独立检查真实导出网表；破坏供电/极性/默认态的反例必须失败。"""
from pathlib import Path
import copy, hashlib, json, xml.etree.ElementTree as ET
P=Path(__file__).resolve().parent

def electrical(d):
 p={v['ref']:v for v in d['parts']}
 def pin(r,n,net): assert p[r]['pins'][str(n)]==net,(r,n,net)
 for r,n,net in [('U1',35,'ADS_PWDN'),('U2',8,'XIAO_PWDN'),('U2',16,'ADS_PWDN'),('J1',15,'XIAO_PWDN'),('J1',16,'OE_N'),('U1',62,'AVDD'),('U12',1,'U7_EN'),('U12',6,'VBAT'),('U12',5,'3V3'),('D1',1,'AVDD'),('D1',2,'DVDD'),('R41',1,'U7_EN'),('R41',2,'EN_RC'),('C24',1,'EN_RC')]:pin(r,n,net)
 for r,net in [('R39','XIAO_PWDN'),('R40','ADS_PWDN')]:
  assert p[r]['value']=='10k';pin(r,1,net);pin(r,2,'GND')
 assert p['U10']['value']=='SN74AUP1T14DCKR'
 assert p['R41']['value']=='4.7k'
 assert 'U11' not in p
 assert not d['manufacturing_ready'] and not d['human_test_ready']
 assert len(p)==208 and all(x['footprint'] for x in p.values())
 assert len(set(x['source_ref'] for x in p.values()))==208
 return p

def check():
 d=json.loads((P/'design.json').read_text());p=electrical(d)
 x=ET.parse(P/'v12-r01.net.xml').getroot()
 comps={c.attrib['ref']:c for c in x.findall('./components/comp')}
 assert set(comps)==set(p),('元件集合不一致',set(comps)^set(p))
 actual={}
 for net in x.findall('./nets/net'):
  name=net.attrib['name']
  for n in net.findall('node'):
   key=(n.attrib['ref'],n.attrib['pin'])
   assert key not in actual,key
   actual[key]=name
 count=0
 for ref,v in p.items():
  assert comps[ref].findtext('footprint')==v['footprint'],ref
  for pin,net in v['pins'].items():
   got=actual.get((ref,pin))
   if net is not None:assert got==net,(ref,pin,net,got);count+=1
   else: assert got is None or got.startswith('unconnected-'),(ref,pin,got)
 baseline=json.loads((P/'baseline.json').read_text())
 assert hashlib.sha256((P/'baseline-design.json').read_bytes()).hexdigest()==baseline['sha256']
 for name,sha in json.loads((P/'footprint-hashes.json').read_text()).items():
  assert hashlib.sha256((P/name).read_bytes()).hexdigest()==sha,name
 failures=[]
 for ref,pin,net in [('U1','35','PG'),('R40','2','ADS_PWDN'),('D1','1','DVDD'),('U12','6','3V3'),('C24','1','U7_EN'),('J1','16','DVDD')]:
  bad=copy.deepcopy(d);next(v for v in bad['parts'] if v['ref']==ref)['pins'][pin]=net
  try:electrical(bad)
  except AssertionError:failures.append(ref+'.'+pin)
  else:raise AssertionError('反例未被发现:'+ref)
 result={'components':len(p),'connected_pins_verified':count,'negative_controls_rejected':failures,'netlist_matches':True,'scope':'静态电气与原生网表；非上电/人体/制造验收'}
 (P/'check-result.json').write_text(json.dumps(result,ensure_ascii=False,indent=2)+'\n')
 print(json.dumps(result,ensure_ascii=False))
if __name__=='__main__':check()
